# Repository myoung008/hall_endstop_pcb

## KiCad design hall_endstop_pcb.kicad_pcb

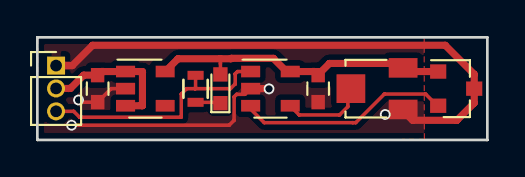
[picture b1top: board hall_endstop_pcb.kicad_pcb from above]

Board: 2 copper layers, 25.0 x 5.7 mm, 9 parts (0 on the bottom side), 7 nets.

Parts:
C1: 1uf; C_0603
C2: 2.2uf; C_0603
D1: LED; LED_0603
P1: CONN_01X03; Pin_Header_Straight_1x03_Pitch1.27mm
R1: 300; R_0603
RV1: POT; Potentiometer_Trimmer-TT22A
U1: AP2204; SOT-23-5
U2: DRV5053; SOT-23
U3: MCP601; SOT-23-5

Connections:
+5V: C2.1, D1.2, RV1.3, U1.5, U2.1, U3.5
+24V: C1.1, P1.2, U1.1, U1.3
GND: C1.2, C2.2, P1.1, RV1.1, U1.2, U2.3, U3.2
unnamed: D1.1, R1.1
unnamed: P1.3, R1.2, U3.1
unnamed: RV1.2, U3.4
unnamed: U2.2, U3.3

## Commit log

2017-04-12 Initial commit. Voltage regulator (U1) and C1 are unnecessary on 5v and 3.3v systems.
2017-04-14 Update datasheets, specific part values in schematic, add BOM
